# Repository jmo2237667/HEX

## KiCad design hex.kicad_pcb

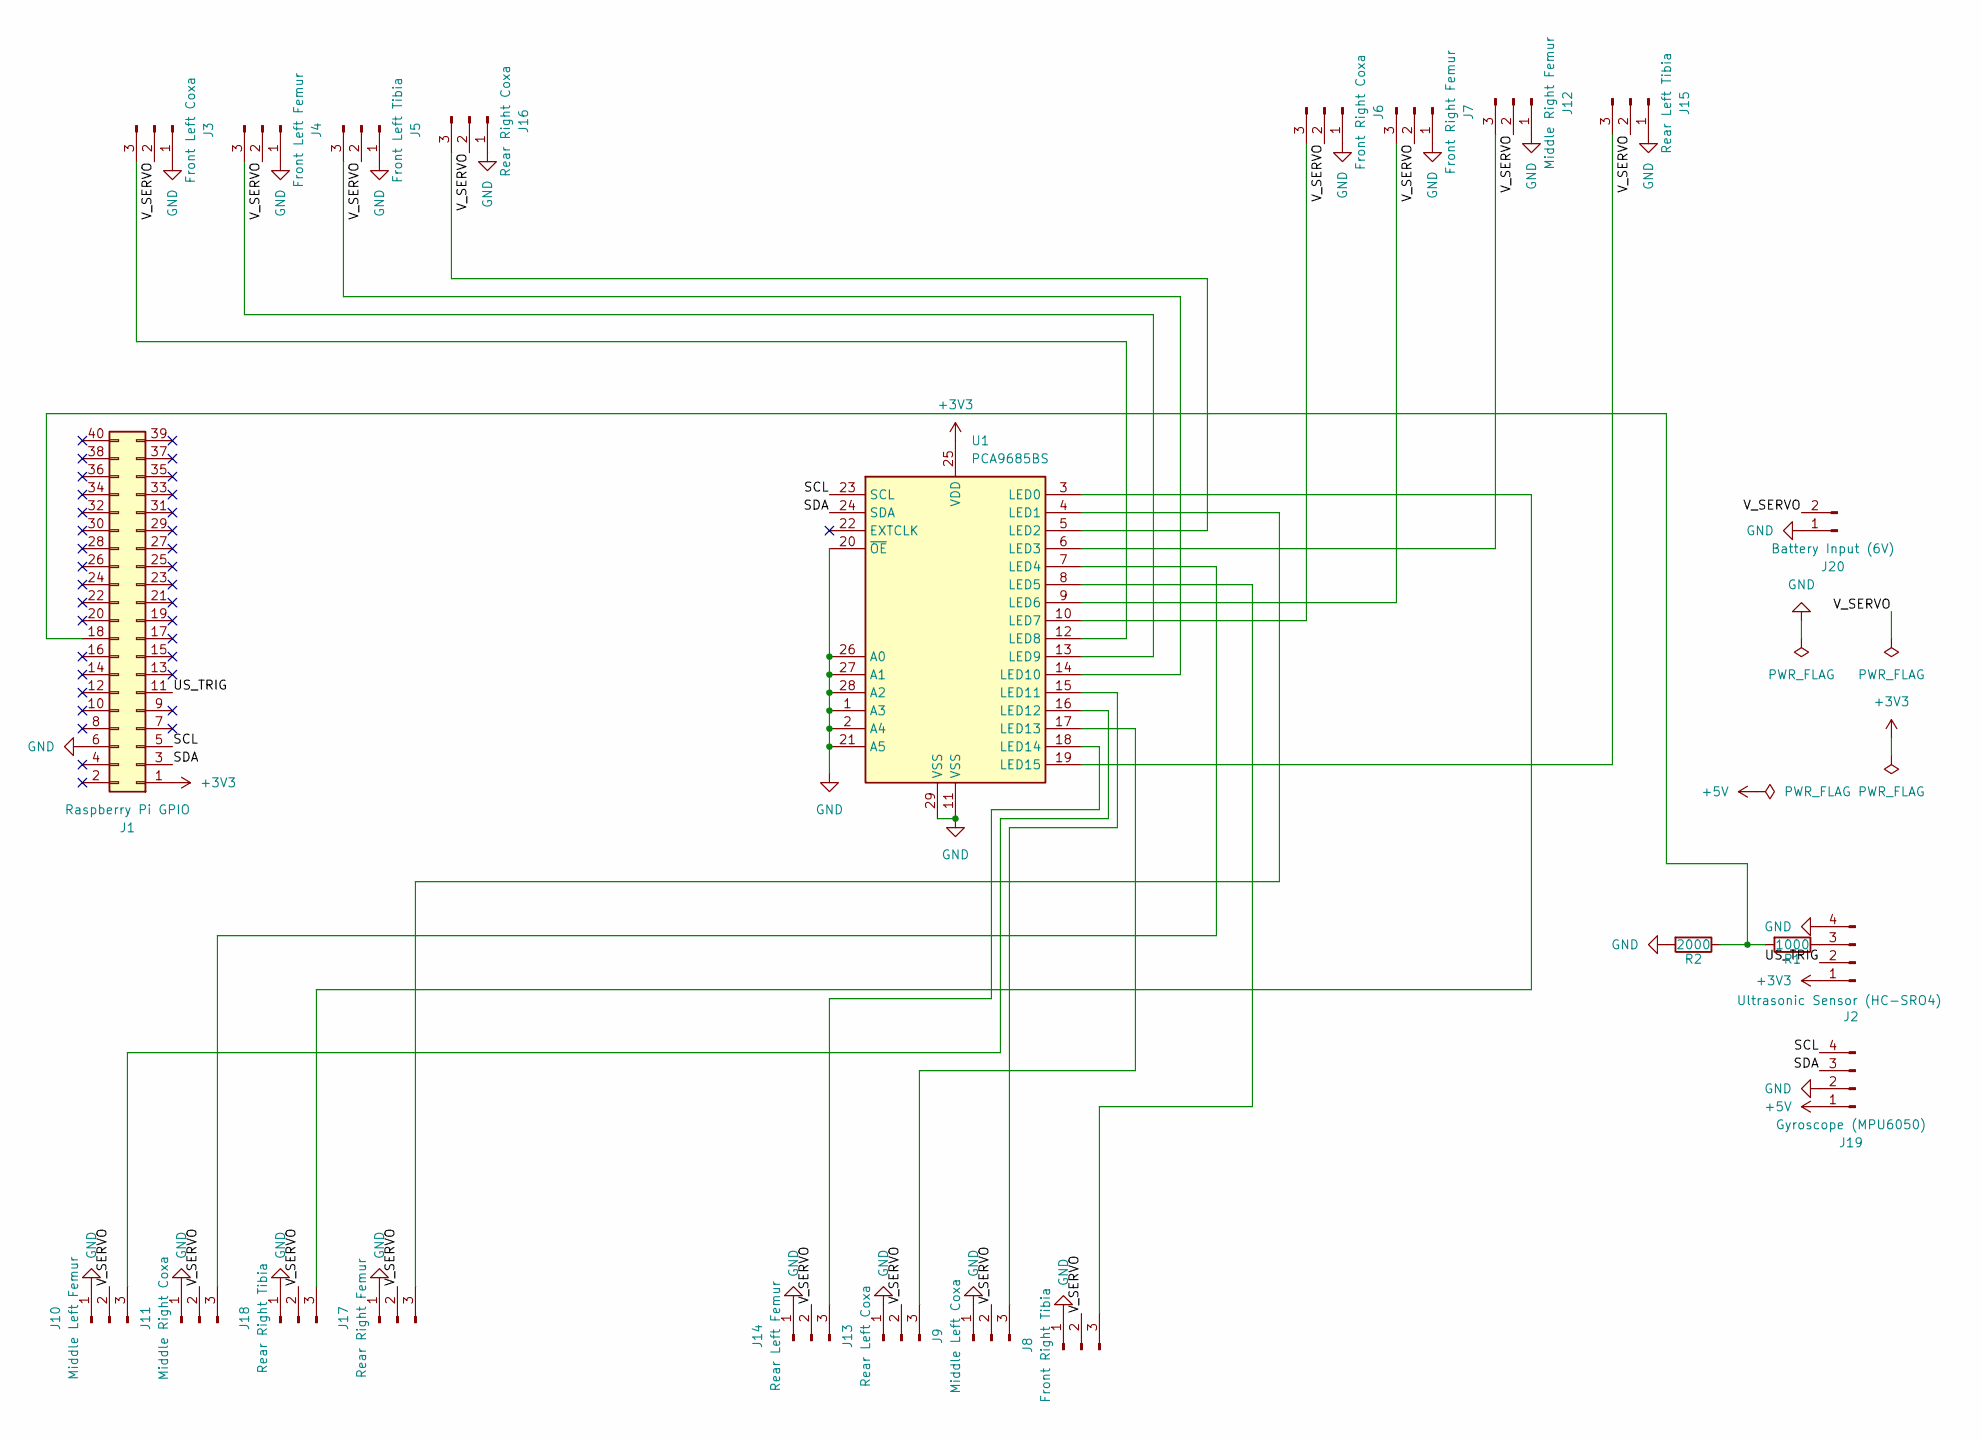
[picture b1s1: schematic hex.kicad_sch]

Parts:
J1: Raspberry Pi GPIO; PinHeader_2x20_P2.54mm_Vertical
J2: Ultrasonic Sensor (HC-SRO4); PinHeader_1x04_P2.54mm_Vertical
J3: Front Left Coxa; PinHeader_1x03_P2.54mm_Vertical
J4: Front Left Femur; PinHeader_1x03_P2.54mm_Vertical
J5: Front Left Tibia; PinHeader_1x03_P2.54mm_Vertical
J6: Front Right Coxa; PinHeader_1x03_P2.54mm_Vertical
J7: Front Right Femur; PinHeader_1x03_P2.54mm_Vertical
J8: Front Right Tibia; PinHeader_1x03_P2.54mm_Vertical
J9: Middle Left Coxa; PinHeader_1x03_P2.54mm_Vertical
J10: Middle Left Femur; PinHeader_1x03_P2.54mm_Vertical
J11: Middle Right Coxa; PinHeader_1x03_P2.54mm_Vertical
J12: Middle Right Femur; PinHeader_1x03_P2.54mm_Vertical
J13: Rear Left Coxa; PinHeader_1x03_P2.54mm_Vertical
J14: Rear Left Femur; PinHeader_1x03_P2.54mm_Vertical
J15: Rear Left Tibia; PinHeader_1x03_P2.54mm_Vertical
J16: Rear Right Coxa; PinHeader_1x03_P2.54mm_Vertical
J17: Rear Right Femur; PinHeader_1x03_P2.54mm_Vertical
J18: Rear Right Tibia; PinHeader_1x03_P2.54mm_Vertical
J19: Gyroscope (MPU6050); PinHeader_1x04_P2.54mm_Vertical
J20: Battery Input (6V); TerminalBlock_TE_282834-2_1x02_P2.54mm_Horizontal
R1: 1000; R_Axial_DIN0207_L6.3mm_D2.5mm_P7.62mm_Horizontal
R2: 2000; R_Axial_DIN0207_L6.3mm_D2.5mm_P7.62mm_Horizontal
U1: PCA9685BS; QFN-28-1EP_6x6mm_P0.65mm_EP4.25x4.25mm

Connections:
+3V3: J1.1, J2.1, U1.25 (VDD)
+5V: J19.1
/SCL: J1.5, J19.4, U1.23 (SCL)
/SDA: J1.3, J19.3, U1.24 (SDA)
/US_TRIG: J1.11, J2.2
/V_SERVO: J3.2, J4.2, J5.2, J6.2, J7.2, J8.2, J9.2, J10.2, J11.2, J12.2, J13.2, J14.2, J15.2, J16.2, J17.2, J18.2, J20.2
GND: J1.6, J2.4, J3.1, J4.1, J5.1, J6.1, J7.1, J8.1, J9.1, J10.1, J11.1, J12.1, J13.1, J14.1, J15.1, J16.1, J17.1, J18.1, J19.2, J20.1, R2.2, U1.1 (A3), U1.2 (A4), U1.11 (VSS), U1.20 (~OE), U1.21 (A5), U1.26 (A0), U1.27 (A1), U1.28 (A2), U1.29 (VSS)
unnamed: J1.18, R1.2, R2.1
unnamed: J2.3, R1.1
unnamed: J3.3, U1.12 (LED8)
unnamed: J4.3, U1.13 (LED9)
unnamed: J5.3, U1.14 (LED10)
unnamed: J6.3, U1.10 (LED7)
unnamed: J7.3, U1.9 (LED6)
unnamed: J8.3, U1.8 (LED5)
unnamed: J9.3, U1.15 (LED11)
unnamed: J10.3, U1.16 (LED12)
unnamed: J11.3, U1.7 (LED4)
unnamed: J12.3, U1.6 (LED3)
unnamed: J13.3, U1.17 (LED13)
unnamed: J14.3, U1.18 (LED14)
unnamed: J15.3, U1.19 (LED15)
unnamed: J16.3, U1.5 (LED2)
unnamed: J17.3, U1.4 (LED1)
unnamed: J18.3, U1.3 (LED0)

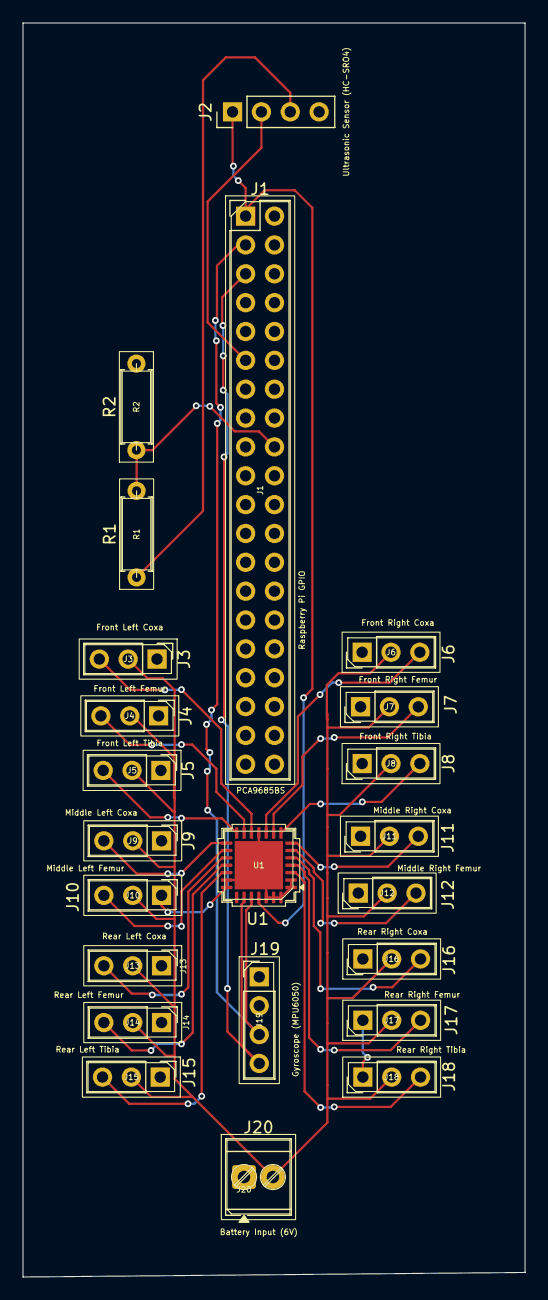
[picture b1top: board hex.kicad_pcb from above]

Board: 2 copper layers, 44.2 x 110.4 mm, 23 parts (0 on the bottom side), 24 nets.

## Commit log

2026-05-28 Create pi
2026-05-28 Update pi
